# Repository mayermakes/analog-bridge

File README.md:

# Analog Bridge

A modular, open hardware 16-channel measurement and logic-monitoring platform built around an ATtiny3226 and four ADS1115 ADCs. The bridge exposes a line-oriented SCPI interface over Ethernet and USB serial, making it useful for automated test fixtures, digital logic observation, and lightweight data acquisition.

> **Status:** Work in progress. The hardware, firmware, and host tools are under active development.

## Features

- 16 single-ended analog inputs per device
- 3.3 V logic-level classification in the included monitor application
- Four ADS1115 converters on a shared I²C bus
- ATtiny3226-based firmware
- Ethernet connectivity through an ENC28J60
- USB-UART access at 115200 8N1
- SCPI commands for identification, channel configuration, status, and measurements
- Python web dashboards for live channel monitoring and oscilloscope-style plotting
- KiCad PCB and schematic sources
- 3D-printable enclosure plates and manufacturing files

## Repository layout

```text
analog-bridge/
├── analog-bridge-PCB/       # KiCad project, schematic, and PCB layout
├── analog-bridge/            # PlatformIO firmware and Python host tools
│   ├── src/                  # Firmware sources
│   ├── include/              # Firmware headers
│   ├── lib/                  # Project libraries
│   ├── test/                 # PlatformIO tests
│   ├── platformio.ini        # Build and upload configuration
│   ├── API_README.md         # Complete SCPI and transport reference
│   ├── analog_bridge_monitor.py
│   └── analog_bridge_oscilloscope.py
└── manufacturing/            # 3MF and SVG enclosure/manufacturing files
```

## Channel mapping

Each ADS1115 contributes four single-ended inputs:

| Logical channels | ADS1115 address | Inputs |
| --- | --- | --- |
| 0–3 | `0x48` | AIN0–AIN3 |
| 4–7 | `0x49` | AIN0–AIN3 |
| 8–11 | `0x4A` | AIN0–AIN3 |
| 12–15 | `0x4B` | AIN0–AIN3 |

The firmware uses the ADS1115 `GAIN_ONE` setting, with a nominal input range of approximately ±4.096 V. Always observe the electrical limits of the ADC and the assembled hardware.

## SCPI interface

The device accepts one command per line. Commands are case-insensitive and can be sent over either transport:

- **Ethernet:** DHCP, TCP port `5025`
- **USB serial:** `115200 8N1`

Example Ethernet session:

```bash
printf '*IDN?\n' | nc 192.168.1.42 5025
printf 'MEAS:RAW? 6\n' | nc 192.168.1.42 5025
```

Frequently used commands include:

| Command | Purpose |
| --- | --- |
| `*IDN?` | Return device identification |
| `*RST` | Restore enabled channels and 16 SPS defaults |
| `SYST:ERR?` | Read and clear the latest error |
| `CONF:CHAN<n>:RATE <sps>` | Set a channel’s sampling rate |
| `CONF:CHAN<n>:STAT ON\|OFF` | Enable or disable a channel |
| `MEAS:RAW? <n>` | Read the latest raw ADC value |
| `MEAS:RAW:ALL?` | Return all 16 channels as CSV records |

Supported rates are 8, 16, 32, 64, 128, 250, 475, and 860 SPS. For the full command reference, wiring information, response formats, and transport details, see [`analog-bridge/API_README.md`](analog-bridge/API_README.md).

> The SCPI interface has no authentication or encryption. Use Ethernet access only on a trusted network.

## Firmware development

The firmware is built with [PlatformIO](https://platformio.org/) and the Arduino framework.

### Prerequisites

- PlatformIO Core or the PlatformIO IDE extension
- An ATtiny3226 UPDI programmer
- `pymcuprog` for UPDI upload:

```bash
python3 -m pip install pymcuprog
```

### Build and upload

From the firmware directory:

```bash
cd analog-bridge
pio run
pio run -e Upload_UPDI -t upload
```

Configure the upload port and speed for your UPDI adapter according to your local setup. The default PlatformIO environment is `Upload_UPDI`.

### ADC diagnostic firmware

The repository includes a direct ADC test firmware that bypasses the normal SCPI scheduler:

```bash
pio run -e ADC_TEST -t upload
```

Open the serial port at `115200 8N1` to view probe and raw conversion output. Use this mode to isolate ADC, I²C, power, address, or wiring problems.

## Python host tools

The host applications use only the Python standard library unless USB serial discovery is needed.

### Live channel monitor

The monitor discovers up to two bridges over Ethernet or USB serial and serves a live 32-channel dashboard. Ethernet discovery scans local IPv4 `/24` networks for TCP port `5025`; USB discovery requires `pyserial`.

```bash
cd analog-bridge
python3 -m pip install pyserial  # optional, required for USB discovery
python3 analog_bridge_monitor.py
```

Open [http://127.0.0.1:8080](http://127.0.0.1:8080). By default, channels are classified as:

- `HIGH`: ≥ 2.00 V
- `LOW`: ≤ 0.80 V
- `doubt`: between the two thresholds

Customize the thresholds, serial port, or web server:

```bash
python3 analog_bridge_monitor.py \
  --serial-port /dev/ttyUSB0 \
  --high 2.2 \
  --low 0.7 \
  --port 8080
```

### Network oscilloscope

The oscilloscope discovers up to four Ethernet bridges and plots AIN0 from each ADS1115: logical channels 0, 4, 8, and 12.

```bash
python3 analog_bridge_oscilloscope.py
```

Open [http://127.0.0.1:8090](http://127.0.0.1:8090). Adjust the rolling history and polling interval with:

```bash
python3 analog_bridge_oscilloscope.py --history 60 --poll 0.1 --port 8090
```

The tools use the device’s millisecond timestamp, which is relative to device boot rather than synchronized Unix time.

## Hardware sources

The KiCad project is in [`analog-bridge-PCB/`](analog-bridge-PCB/). It includes the main PCB, project configuration, and analog-section schematic. Manufacturing and enclosure assets are in [`manufacturing/`](manufacturing/), including SVG and 3MF files.

The primary ATtiny3226 connections are:

| Function | Pin |
| --- | --- |
| I²C SCL | PB0 |
| I²C SDA | PB1 |
| UART TX | PB2 |
| UART RX | PB3 |
| ADS alert 0–3 | PB4, PB5, PC0, PC1 |
| ENC28J60 MOSI/MISO/SCK | PA1, PA2, PA3 |
| ENC28J60 CS/INT | PA4, PA6 |
| UPDI | PA0 |

## Safety and limitations

- Verify input voltage, grounding, and signal integrity before connecting external equipment.
- The analog inputs are not isolated and the SCPI network service is unauthenticated.
- Measurement rates are per-channel scheduling targets; use returned timestamps to determine the achieved rate.
- Configuration is held in RAM and returns to the default state after reset or power loss.

## Contributing

Issues and pull requests are welcome. When reporting a hardware or firmware problem, include the board revision, firmware environment, transport used, wiring, and relevant serial or SCPI output.

## License

This project is licensed under the [Open Community License v1.1 (OCL v1.1)](LICENSE), without add-on conditions.

OCL v1.1 grants non-commercial users the right to use, copy, modify, and repair the project and requires distributed derivatives to remain under OCL. Commercial business use is limited to internal use unless a separate business or repair license is obtained. See [`LICENSE`](LICENSE) for the complete terms.

Third-party components and dependencies distributed with or alongside this project remain under their respective licenses where those licenses are incompatible with OCL. The authoritative OCL text and available add-ons are maintained by the [OpenCommunityLicence project](https://github.com/OpenCommunityLicence/OpenCommunityLicence).

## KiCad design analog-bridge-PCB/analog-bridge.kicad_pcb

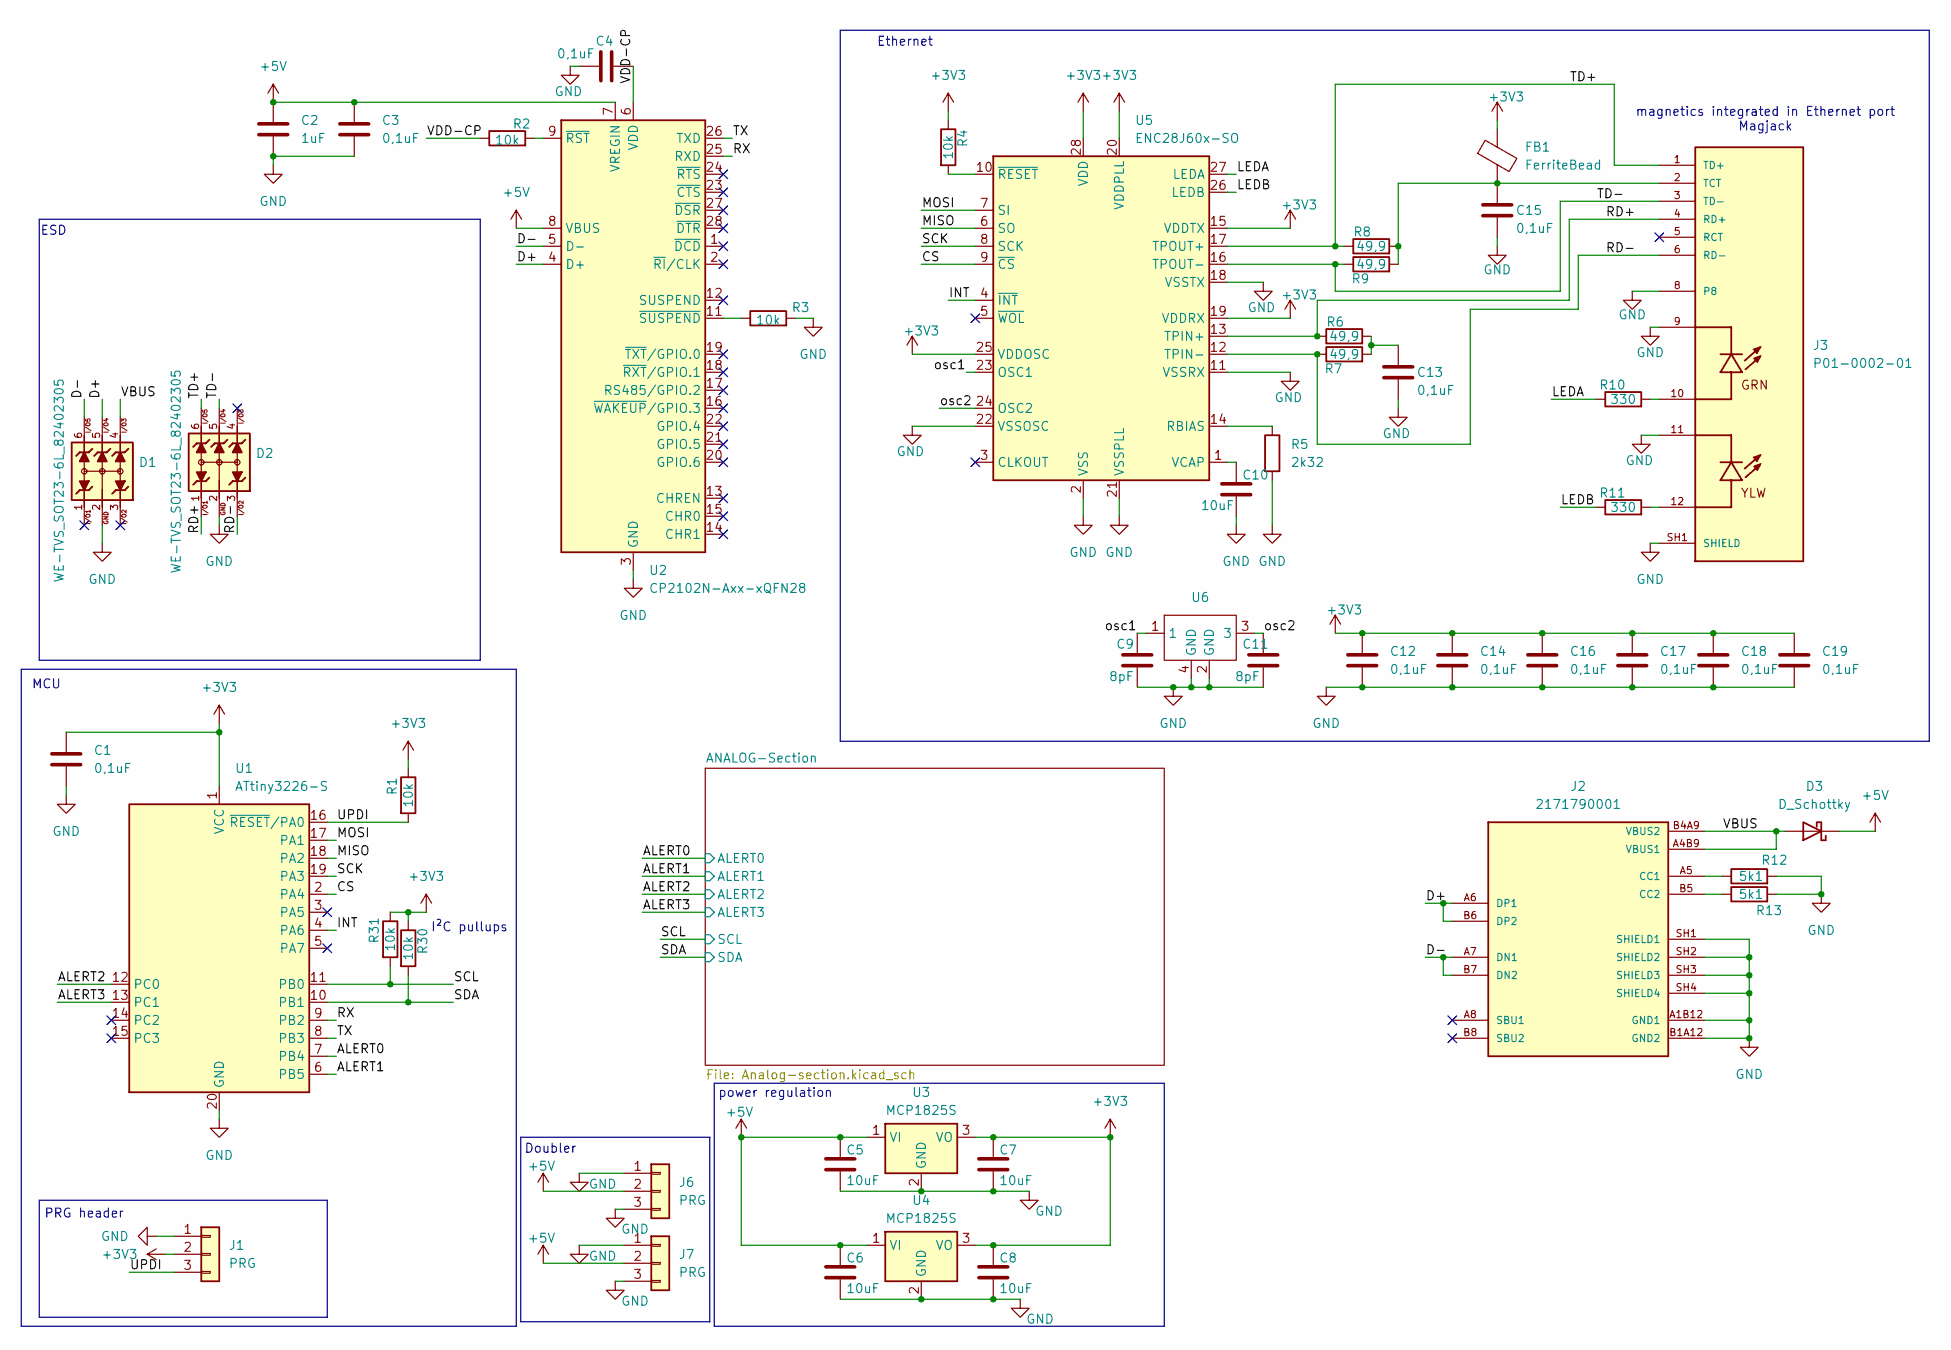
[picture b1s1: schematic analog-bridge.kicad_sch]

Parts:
C1, C3, C4, C12, C13, C14, C15, C16, C17, C18, C19: 0,1uF; C_0603_1608Metric
C2: 1uF; C_0603_1608Metric
C5, C6, C7, C8, C10: 10uF; C_0603_1608Metric
C9, C11: 8pF; C_0603_1608Metric
D1, D2: WE-TVS_SOT23-6L_82402305; WE-TVS_SOT23-6L
D3: D_Schottky; D_0603_1608Metric
FB1: FerriteBead; L_0603_1608Metric
J1, J6, J7: PRG; PinHeader_1x03_P2.54mm_Vertical
J2: 2171790001; MOLEX_2171790001; PARTREV A1
J3: P01-0002-01; BEL_P01-0002-01; PARTREV 1
R1, R2, R3, R4, R30, R31: 10k; R_0603_1608Metric
R5: 2k32; R_0603_1608Metric
R6, R7, R8, R9: 49,9; R_0603_1608Metric
R10, R11: 330; R_0603_1608Metric
R12, R13: 5k1; R_0603_1608Metric
U1: ATtiny3226-S; SOIC-20W_7.5x12.8mm_P1.27mm
U2: CP2102N-Axx-xQFN28; QFN-28-1EP_5x5mm_P0.5mm_EP3.35x3.35mm
U3, U4: MCP1825S; SOT-223-3_TabPin2
U5: ENC28J60x-SO; SOIC-28W_7.5x18.7mm_P1.27mm
U6: Crystal_SMD_2520-4Pin_2.5x2.0mm

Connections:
+3V3: C1.1, C7.1, C8.1, C12.1, C14.1, C16.1, C17.1, C18.1, C19.1, FB1.1, J1.2, R1.1, R4.1, R30.1, R31.1, U1.1 (VCC), U3.3 (VO), U4.3 (VO), U5.15 (VDDTX), U5.19 (VDDRX), U5.20 (VDDPLL), U5.25 (VDDOSC), U5.28 (VDD); also elsewhere on the board
+5V: C2.1, C3.1, C5.1, C6.1, D3.1 (K), J6.2, J7.2, U2.7 (VREGIN), U2.8 (VBUS), U3.1 (VI), U4.1 (VI)
/ALERT0: U1.7 (PB4); also elsewhere on the board
/ALERT1: U1.6 (PB5); also elsewhere on the board
/ALERT2: U1.12 (PC0); also elsewhere on the board
/ALERT3: U1.13 (PC1); also elsewhere on the board
/CS: U1.2 (PA4), U5.9 (~CS)
/D+: D1.5, J2.A6 (DP1), J2.B6 (DP2), U2.4 (D+)
/D-: D1.6, J2.A7 (DN1), J2.B7 (DN2), U2.5 (D-)
/INT: U1.4 (PA6), U5.4 (~INT)
/LEDA: R10.1, U5.27 (LEDA)
/LEDB: R11.1, U5.26 (LEDB)
/MISO: U1.18 (PA2), U5.6 (SO)
/MOSI: U1.17 (PA1), U5.7 (SI)
/RD+: D2.1, J3.4 (RD+), R6.1, U5.13 (TPIN+)
/RD-: D2.3, J3.6 (RD-), R7.1, U5.12 (TPIN-)
/RX: U1.9 (PB2), U2.25 (RXD)
/SCK: U1.19 (PA3), U5.8 (SCK)
/SCL: R31.2, U1.11 (PB0); also elsewhere on the board
/SDA: R30.2, U1.10 (PB1); also elsewhere on the board
/TD+: D2.6, J3.1 (TD+), R8.1, U5.17 (TPOUT+)
/TD-: D2.5, J3.3 (TD-), R9.1, U5.16 (TPOUT-)
/TX: U1.8 (PB3), U2.26 (TXD)
/UPDI: J1.3, R1.2, U1.16 (~RESET/PA0)
/VBUS: D1.4, D3.2 (A), J2.A4B9 (VBUS1), J2.B4A9 (VBUS2)
/VDD-CP: C4.2, R2.1, U2.6 (VDD)
/osc1: C9.1, U5.23 (OSC1), U6.1
/osc2: C11.1, U5.24 (OSC2), U6.3
GND: C1.2, C2.2, C3.2, C4.1, C5.2, C6.2, C7.2, C8.2, C9.2, C10.2, C11.2, C12.2, C13.2, C14.2, C15.2, C16.2, C17.2, C18.2, C19.2, D1.2, D2.2, J1.1, J2.A1B12 (GND1), J2.B1A12 (GND2), J2.SH1 (SHIELD1), J2.SH2 (SHIELD2), J2.SH3 (SHIELD3), J2.SH4 (SHIELD4), J3.8, J3.9, J3.11, J3.SH1 (SHIELD), J3.SH2 (SHIELD), J6.1, J6.3, J7.1, J7.3, R3.2, R5.2, R12.2, R13.2, U1.20 (GND), U2.3 (GND), U2.29 (GND), U3.2 (GND), U4.2 (GND), U5.2 (VSS), U5.11 (VSSRX), U5.18 (VSSTX), U5.21 (VSSPLL), U5.22 (VSSOSC), U6.2 (GND), U6.4 (GND); also elsewhere on the board
unnamed: C13.1, R6.2, R7.2
unnamed: J2.A5 (CC1), R12.1
unnamed: J2.B5 (CC2), R13.1
unnamed: J3.10, R10.2
unnamed: J3.12, R11.2
unnamed: C15.1, FB1.2, J3.2 (TCT), R8.2, R9.2
unnamed: R2.2, U2.9 (~RST)
unnamed: R3.1, U2.11 (~SUSPEND)
unnamed: R5.1, U5.14 (RBIAS)
unnamed: C10.1, U5.1 (VCAP)
unnamed: R4.2, U5.10 (~RESET)

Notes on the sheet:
power regulation
Doubler
PRG header
Ethernet
ESD
I²C pullups
MCU
magnetics integrated in Ethernet port Magjack

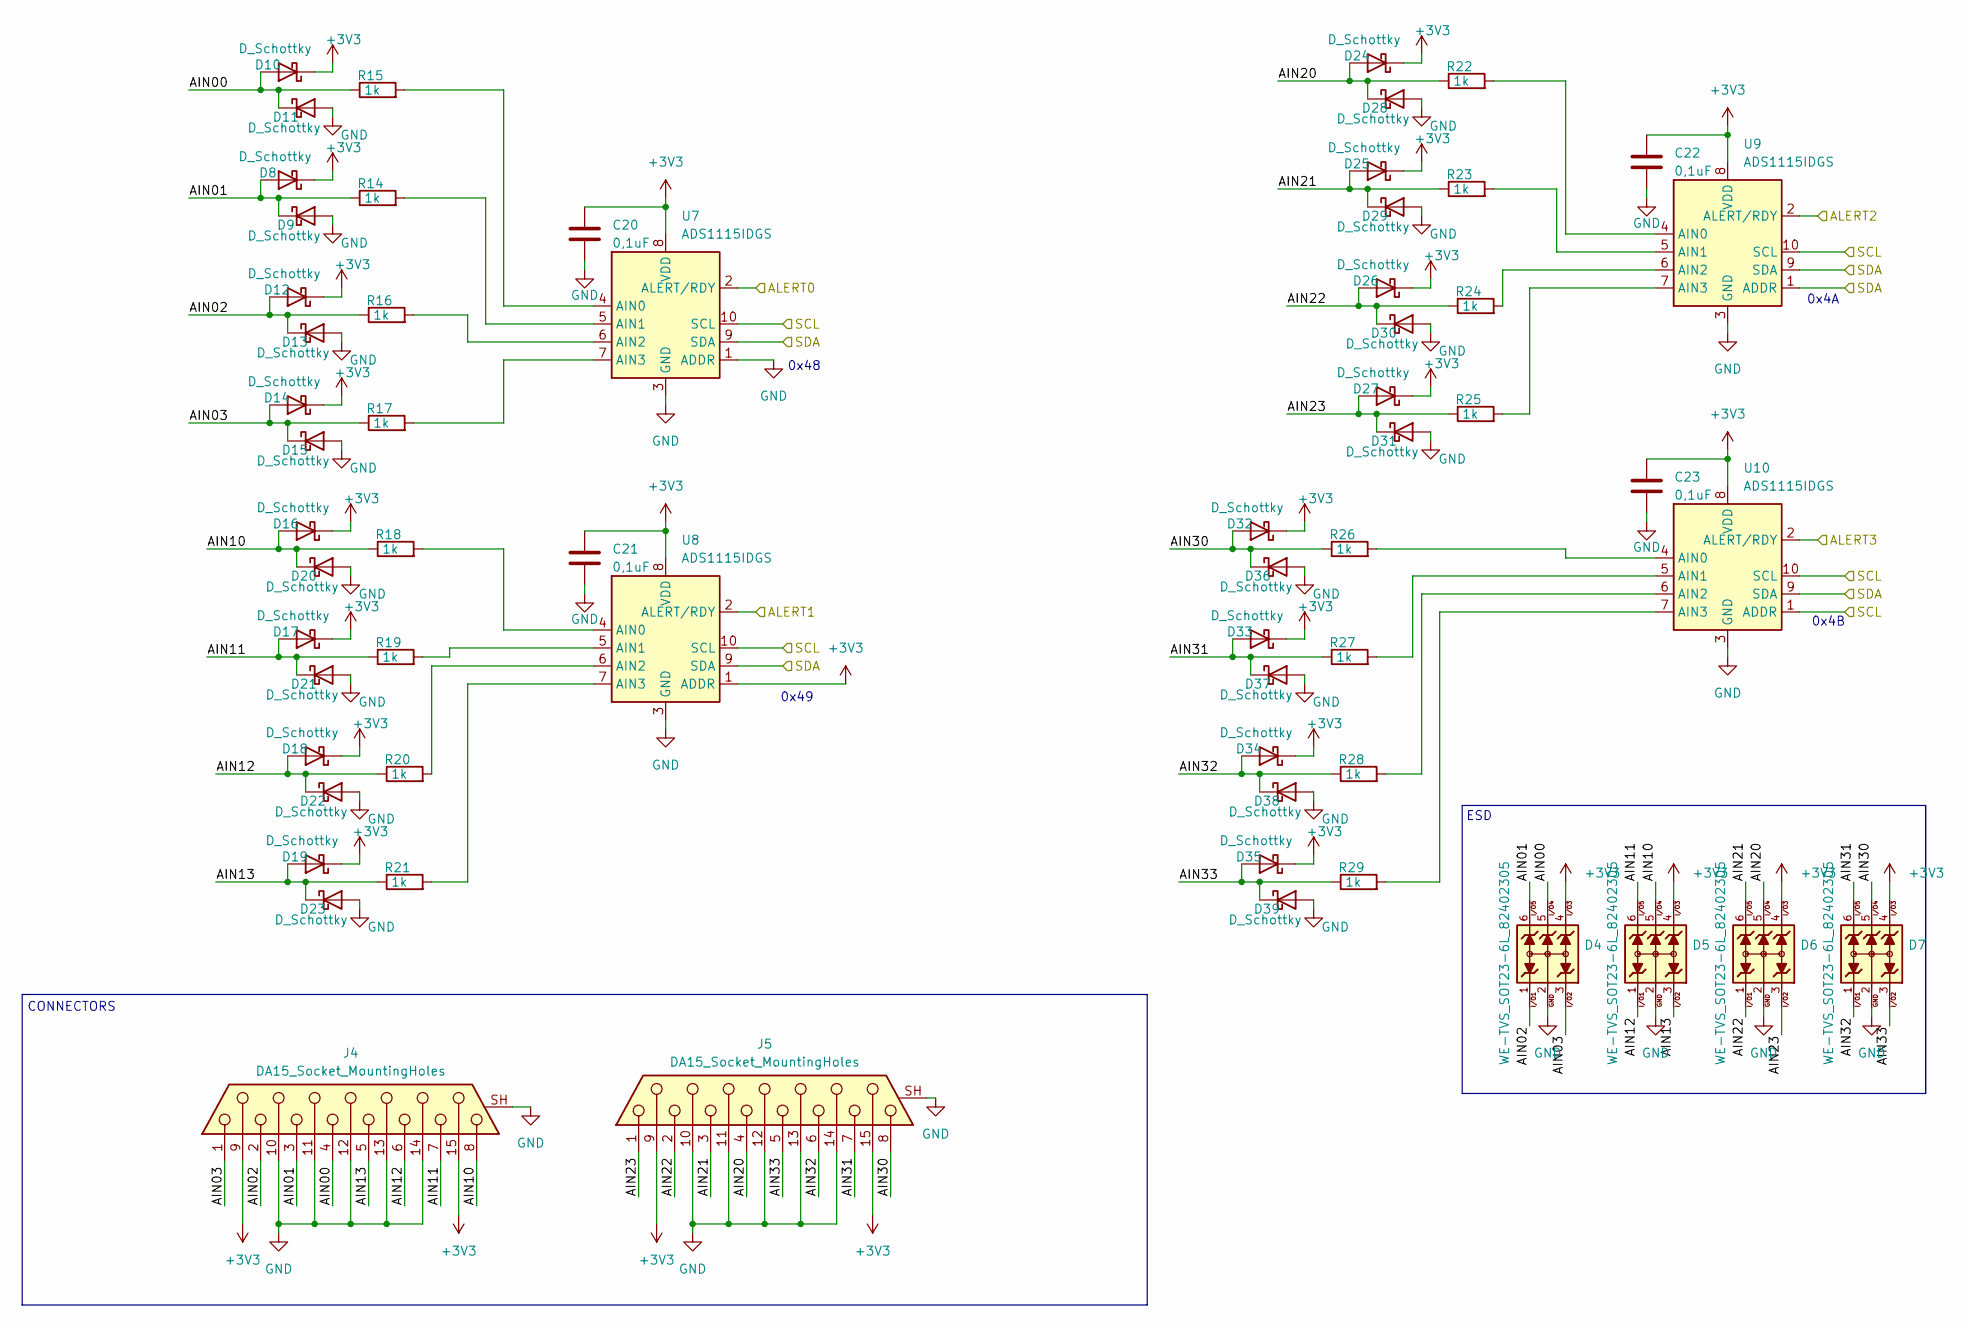
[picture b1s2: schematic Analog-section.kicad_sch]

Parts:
C20, C21, C22, C23: 0,1uF; C_0603_1608Metric
D4, D5, D6, D7: WE-TVS_SOT23-6L_82402305; WE-TVS_SOT23-6L
D8, D9, D10, D11, D12, D13, D14, D15, D16, D17, D18, D19, D20, D21, D22, D23, D24, D25, D26, D27, D28, D29, D30, D31, D32, D33, D34, D35, D36, D37, D38, D39: D_Schottky; D_0603_1608Metric
J4, J5: DA15_Socket_MountingHoles; DSUB-15_Socket_Horizontal_P2.77x2.84mm_EdgePinOffset7.70mm_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
R14, R15, R16, R17, R18, R19, R20, R21, R22, R23, R24, R25, R26, R27, R28, R29: 1k; R_0603_1608Metric
U7, U8, U9, U10: ADS1115IDGS; TSSOP-10_3x3mm_P0.5mm

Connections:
+3V3: C20.1, C21.1, C22.1, C23.1, D4.4, D5.4, D6.4, D7.4, D8.1 (K), D10.1 (K), D12.1 (K), D14.1 (K), D16.1 (K), D17.1 (K), D18.1 (K), D19.1 (K), D24.1 (K), D25.1 (K), D26.1 (K), D27.1 (K), D32.1 (K), D33.1 (K), D34.1 (K), D35.1 (K), J4.9, J4.15, J5.9, J5.15, U7.8 (VDD), U8.1 (ADDR), U8.8 (VDD), U9.8 (VDD), U10.8 (VDD); also elsewhere on the board
/ALERT0: U7.2 (ALERT/RDY); also elsewhere on the board
/ALERT1: U8.2 (ALERT/RDY); also elsewhere on the board
/ALERT2: U9.2 (ALERT/RDY); also elsewhere on the board
/ALERT3: U10.2 (ALERT/RDY); also elsewhere on the board
/ANALOG-Section/AIN00: D4.5, D10.2 (A), D11.1 (K), J4.4, R15.1
/ANALOG-Section/AIN01: D4.6, D8.2 (A), D9.1 (K), J4.3, R14.1
/ANALOG-Section/AIN02: D4.1, D12.2 (A), D13.1 (K), J4.2, R16.1
/ANALOG-Section/AIN03: D4.3, D14.2 (A), D15.1 (K), J4.1, R17.1
/ANALOG-Section/AIN10: D5.5, D16.2 (A), D20.1 (K), J4.8, R18.1
/ANALOG-Section/AIN11: D5.6, D17.2 (A), D21.1 (K), J4.7, R19.1
/ANALOG-Section/AIN12: D5.1, D18.2 (A), D22.1 (K), J4.6, R20.1
/ANALOG-Section/AIN13: D5.3, D19.2 (A), D23.1 (K), J4.5, R21.1
/ANALOG-Section/AIN20: D6.5, D24.2 (A), D28.1 (K), J5.4, R22.1
/ANALOG-Section/AIN21: D6.6, D25.2 (A), D29.1 (K), J5.3, R23.1
/ANALOG-Section/AIN22: D6.1, D26.2 (A), D30.1 (K), J5.2, R24.1
/ANALOG-Section/AIN23: D6.3, D27.2 (A), D31.1 (K), J5.1, R25.1
/ANALOG-Section/AIN30: D7.5, D32.2 (A), D36.1 (K), J5.8, R26.1
/ANALOG-Section/AIN31: D7.6, D33.2 (A), D37.1 (K), J5.7, R27.1
/ANALOG-Section/AIN32: D7.1, D34.2 (A), D38.1 (K), J5.6, R28.1
/ANALOG-Section/AIN33: D7.3, D35.2 (A), D39.1 (K), J5.5, R29.1
/SCL: U7.10 (SCL), U8.10 (SCL), U9.10 (SCL), U10.1 (ADDR), U10.10 (SCL); also elsewhere on the board
/SDA: U7.9 (SDA), U8.9 (SDA), U9.1 (ADDR), U9.9 (SDA), U10.9 (SDA); also elsewhere on the board
GND: C20.2, C21.2, C22.2, C23.2, D4.2, D5.2, D6.2, D7.2, D9.2 (A), D11.2 (A), D13.2 (A), D15.2 (A), D20.2 (A), D21.2 (A), D22.2 (A), D23.2 (A), D28.2 (A), D29.2 (A), D30.2 (A), D31.2 (A), D36.2 (A), D37.2 (A), D38.2 (A), D39.2 (A), J4.10, J4.11 (P111), J4.12, J4.13, J4.14, J4.SH (PAD), J5.10, J5.11 (P111), J5.12, J5.13, J5.14, J5.SH (PAD), U7.1 (ADDR), U7.3 (GND), U8.3 (GND), U9.3 (GND), U10.3 (GND); also elsewhere on the board
unnamed: R15.2, U7.4 (AIN0)
unnamed: R14.2, U7.5 (AIN1)
unnamed: R16.2, U7.6 (AIN2)
unnamed: R17.2, U7.7 (AIN3)
unnamed: R18.2, U8.4 (AIN0)
unnamed: R19.2, U8.5 (AIN1)
unnamed: R20.2, U8.6 (AIN2)
unnamed: R21.2, U8.7 (AIN3)
unnamed: R22.2, U9.4 (AIN0)
unnamed: R23.2, U9.5 (AIN1)
unnamed: R24.2, U9.6 (AIN2)
unnamed: R25.2, U9.7 (AIN3)
unnamed: R26.2, U10.4 (AIN0)
unnamed: R27.2, U10.5 (AIN1)
unnamed: R28.2, U10.6 (AIN2)
unnamed: R29.2, U10.7 (AIN3)

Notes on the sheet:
0x4A
ESD
CONNECTORS
0x48
0x49
0x4B

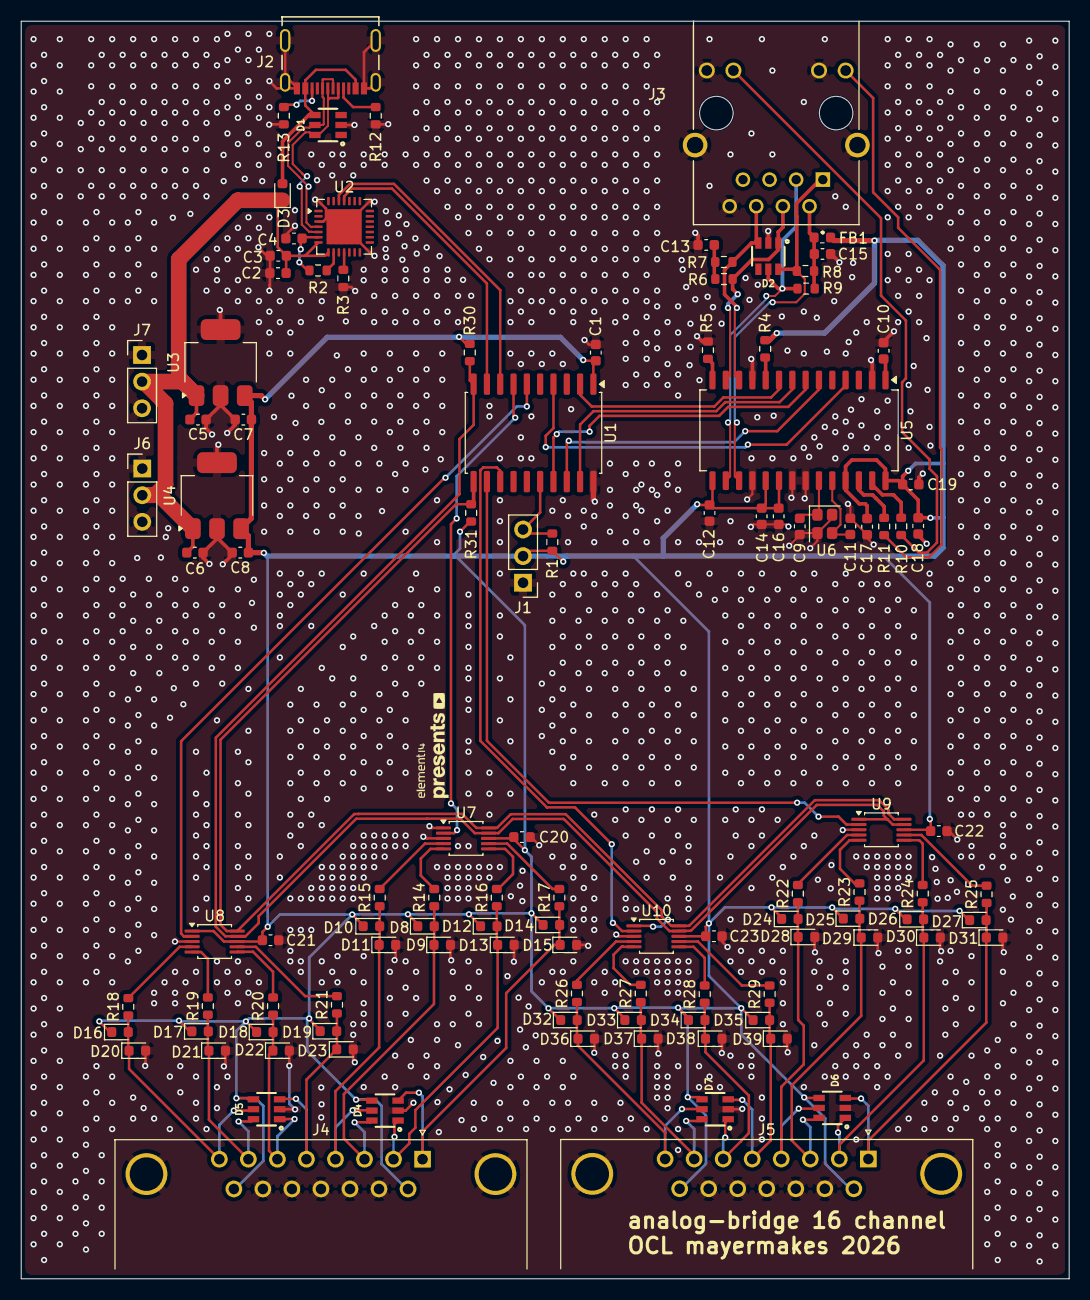
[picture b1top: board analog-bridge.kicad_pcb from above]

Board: 2 copper layers, 100.0 x 120.0 mm, 112 parts (0 on the bottom side), 72 nets.

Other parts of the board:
Ref**: Val**; e14presents logo 10mm silk only v1

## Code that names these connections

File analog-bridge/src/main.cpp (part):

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#include <SPI.h>
#include <Wire.h>

// ATtiny3226 wiring. PA0 remains dedicated to UPDI.
constexpr uint8_t ENC28J60_CS = PIN_PA4;
constexpr uint8_t ENC28J60_INT = PIN_PA6;
constexpr uint8_t ADS_ALERT_PINS[4] = {PIN_PB4, PIN_PB5, PIN_PC0, PIN_PC1};
constexpr uint8_t ADS_ADDRESSES[4] = {0x48, 0x49, 0x4A, 0x4B};
constexpr uint16_t ADS_SINGLE_MUX[4] = {
  ADS1X15_REG_CONFIG_MUX_SINGLE_0,
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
